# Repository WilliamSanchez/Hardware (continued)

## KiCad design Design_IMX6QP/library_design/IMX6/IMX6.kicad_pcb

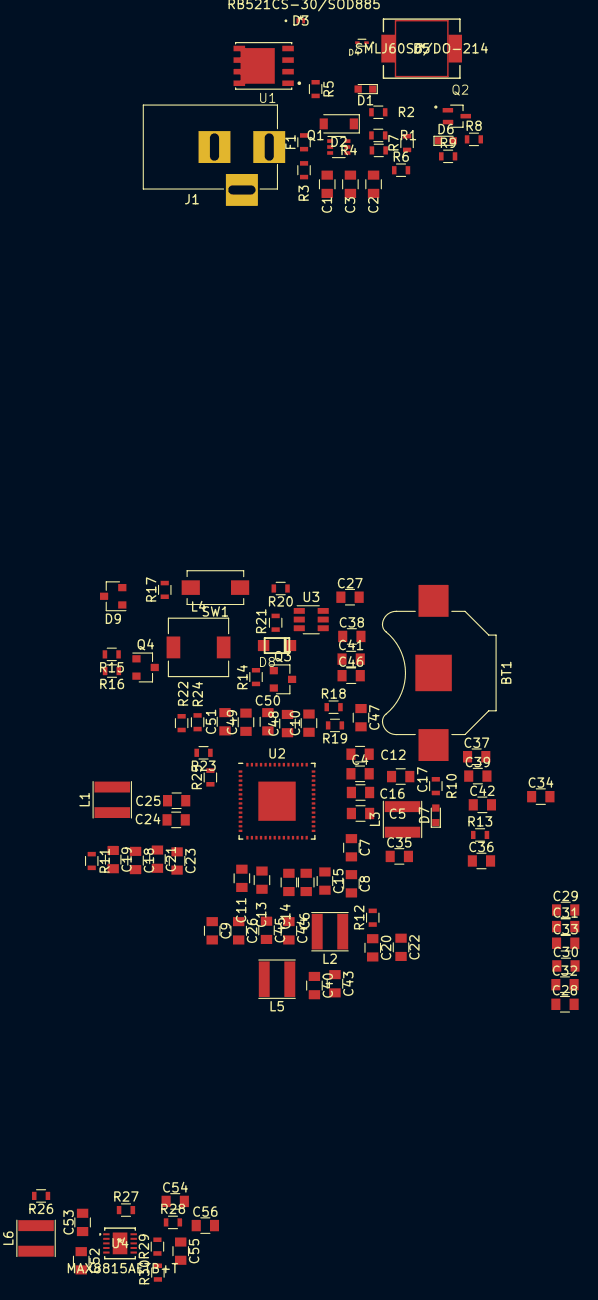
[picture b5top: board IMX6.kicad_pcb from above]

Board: 2 copper layers, 113 parts (0 on the bottom side), 71 nets, no tracks yet.

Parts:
BT1: Battery_Cell; Keystone_3000_1x12mm-CoinCell
C1: 100uF; C_0805
C2: 10uF; C_0805
C3: 1uF; C_0805
C4, C6, C9, C10: 0.47uF; C_0805
C5, C48, C50, C51: 1.0uF; C_0805
C7, C8, C12, C20, C22, C28, C29, C30, C31, C32, C33, C52, C53, C54, C56: 0.1uF; C_0805
C11, C13, C14, C15, C16, C17, C24, C25, C26, C27, C34, C35, C38, C40, C41, C43, C44, C45, C46: 4.7uF; C_0805
C18, C19, C21, C23, C36, C37, C39, C42, C55: 22uF; C_0805
C47: 10.0uF; C_0805
C49: 0.22uF; C_0805
D1, D6, D7: GREEN; LED_0603
D2: MMSZ5231BT1G; D_SOD-123
D3: RB521CS-30/SOD885; RB521CS30L_315
D4: ESD9L5/SOD-923; SODFL1006X40N
D5: SMLJ60S6/DO-214; SMLJ60S1-TP
D8: MBR140SFT; SOD-123FL
D9: BAT54C; SOT-23
F1: F500; R_0603
J1: 5V; BARREL_JACK
L1, L2, L3, L5: 1uH; L_Taiyo-Yuden_NR-40xx
L4: 2.2uH; L_6.3x6.3_H3
L6: 1.2uH; L_Taiyo-Yuden_NR-40xx
Q1: MBT3906DW1; SOT-363_SC-70-6
Q2: NTS4001NT1G; SOT65P220X100-3N
Q3: IRLML6402; SOT-23
Q4: 2N7002; SOT-23
R1, R6: 2.7K; R_0603
R2, R4: 100K; R_0603
R3, R7, R18, R19, R20, R21, R22, R24: 10K; R_0603
R5: 1.8K; R_0603
R8: 470K; R_0603
R9: 820; R_0603
R10, R14, R26, R27: 270; R_0603
R11, R12, R13: 0.02; R_0603
R15, R16: 10.0K; R_0603
R17, R29, R30: 0; R_0603
R23, R25: 68K; R_0603
R28: 100; R_0603
SW1: POWER; SW_SPST_EVQPE1
U1: FDMS6681Z; TRANS_FDMS0300S
U2: MMPF0100; QFN-56_EP_8x8_Pitch0.5mm
U3: FDC6321C_NL; TSOT-23-6
U4: MAX8815AETB+T; MAX8815AETB&plus_T

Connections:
GND: BT1.2, C1.2, C2.2, C3.2, C4.2, C5.2, C6.2, C8.2, C9.2, C10.2, C11.2, C12.2, C13.2, C14.2, C15.2, C16.2, C17.2, C18.2, C19.2, C20.2, C21.2, C22.2, C23.2, C24.2, C25.2, C26.2, C27.2, C28.2, C29.2, C30.2, C31.2, C32.2, C33.2, C34.2, C35.2, C36.2, C37.2, C38.2, C39.2, C40.2, C41.2, C42.2, C43.2, C44.2, C45.2, C46.2, C47.2, C48.2, C49.2, C50.2, C51.2, C52.2, C53.2, C54.2, C55.2, C56.2, D2.2, D4.2, D6.1, D7.1, J1.2, J1.3, Q2.2, R4.2, R8.2, R19.1, R20.2, R26.1, R27.1, R30.1, SW1.1, U2.5, U2.7, U2.14, U2.24, U2.25, U2.32, U2.48, U3.5, U4.5, U4.11
unnamed: BT1.1, C12.1, U2.42
unnamed: C1.1, C2.1, C3.1, D5.1, R9.1
unnamed: C4.1, U2.40
unnamed: C5.1, U2.31
unnamed: C6.1, U2.27
unnamed: C7.1, U2.30
unnamed: C7.2, C8.1, U2.29
unnamed: C9.1, U2.17
unnamed: C10.1, U2.43
unnamed: C11.1, U2.16
unnamed: C13.1, U2.18
unnamed: C14.1, U2.26
unnamed: C15.1, U2.28
unnamed: C16.1, U2.39
unnamed: C17.1, R10.2, U2.41
unnamed: C18.1, C19.1, C21.1, C23.1, L1.1, R11.1
unnamed: C20.1, C22.1, L2.1, R12.1
unnamed: C24.1, U2.12
unnamed: C25.1, U2.10
unnamed: C26.1, U2.23
unnamed: C28.1, C29.1, C30.1, C31.1, C32.1, C33.1
unnamed: C34.1, U2.37
unnamed: C35.1, U2.34
unnamed: C36.1, C37.1, C39.1, C42.1, L3.1, R13.1
unnamed: C38.1, C41.1, L4.1, Q3.3, U2.45
unnamed: C40.1, C43.1, L5.1
unnamed: C44.1, C45.1, U2.20
unnamed: C46.1, D8.1
unnamed: C47.1, R18.2
unnamed: C48.1, U2.49
unnamed: C49.1, U2.52
unnamed: C50.1, U2.51
unnamed: C51.1, U2.50
unnamed: C52.1, C53.1, L6.1, U4.3
unnamed: C54.1, R28.1, U4.7
unnamed: C55.1, C56.1, R28.2, R29.2, U4.9, U4.10
unnamed: D1.1, Q2.3
unnamed: D1.2, R5.2
unnamed: D2.1, R1.2, R3.1
unnamed: D3.1, Q1.4, R8.1, U1.4
unnamed: D3.2, Q1.1
unnamed: D4.1, D5.2, U1.5
unnamed: D6.2, R9.2
unnamed: D7.2, R10.1
unnamed: D8.2, L4.2
unnamed: D9.1, R21.2, U3.3, U3.6
unnamed: D9.3, R17.2, SW1.2
unnamed: F1.1, J1.1
unnamed: F1.2, Q1.3, Q1.6, R1.1, R6.1, U1.1, U1.2, U1.3
unnamed: L1.2, U2.8, U2.9, U2.11
unnamed: L2.2, U2.22
unnamed: L3.2, U2.35, U2.36
unnamed: L5.2, U2.21
unnamed: L6.2, U4.1, U4.2
unnamed: Q1.2, R3.2
unnamed: Q1.5, R7.2
unnamed: Q2.1, R2.2, R4.1
unnamed: Q3.1, Q4.3, R14.1
unnamed: Q3.2, R14.2
unnamed: Q4.1, R15.1, R16.1
unnamed: R6.2, R7.1
unnamed: R18.1, R19.2, U2.47
unnamed: R20.1, U3.1
unnamed: R21.1, U3.2
unnamed: R22.1, R24.2, U2.56
unnamed: R23.1, U2.1
unnamed: R25.1, U2.4
unnamed: R26.2, U4.4
unnamed: R27.2, U4.8
unnamed: R29.1, R30.2, U4.6

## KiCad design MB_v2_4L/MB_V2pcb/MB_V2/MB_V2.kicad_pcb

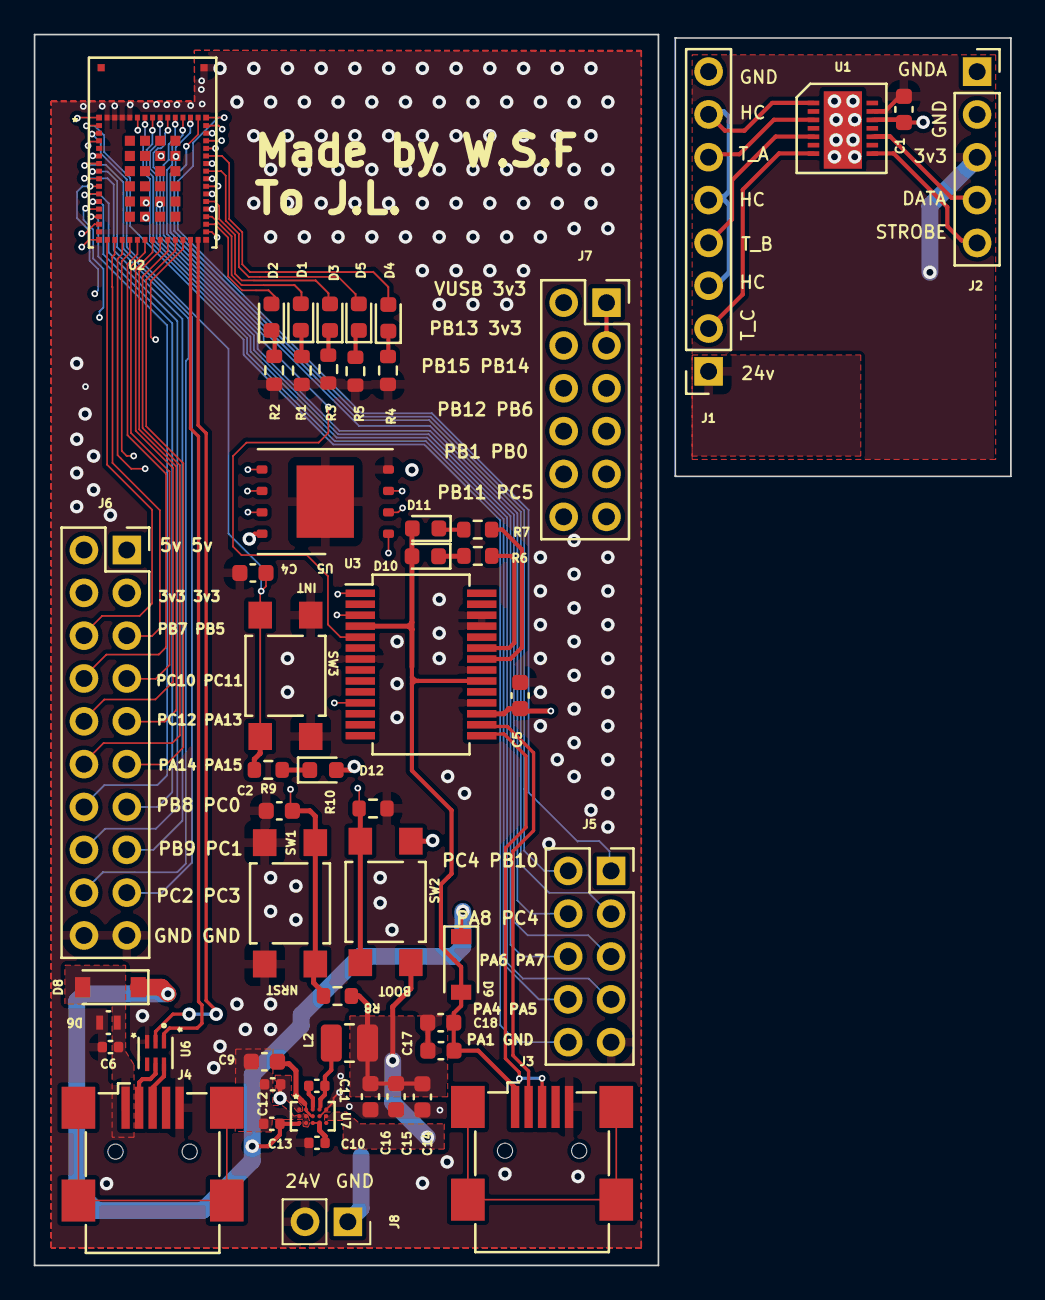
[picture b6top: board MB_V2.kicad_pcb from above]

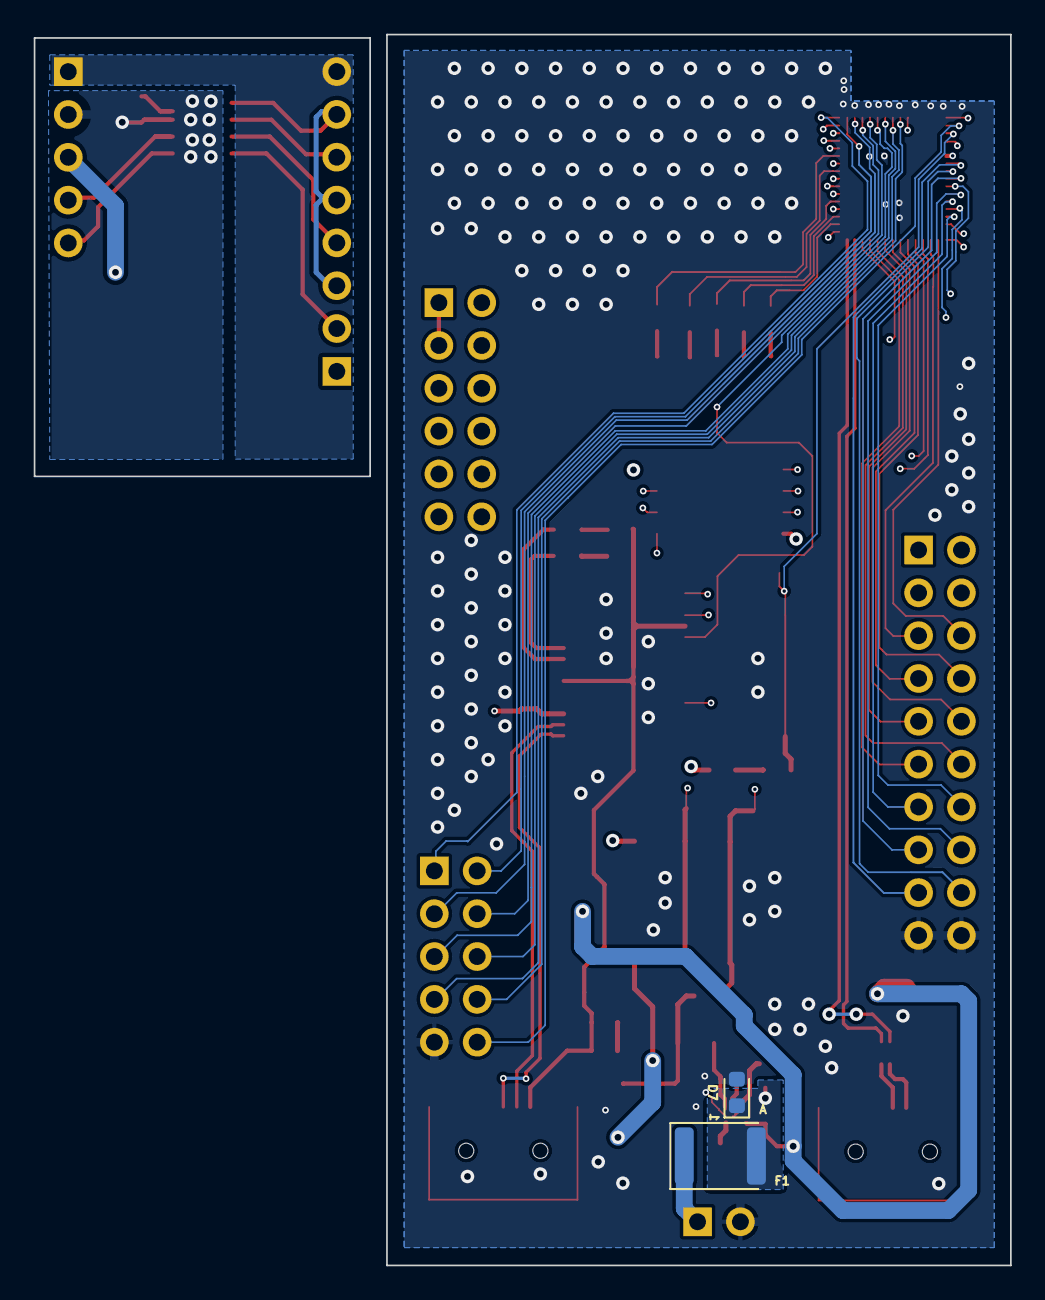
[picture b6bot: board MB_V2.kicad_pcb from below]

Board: 4 copper layers, 57.9 x 73.0 mm, 56 parts (2 on the bottom side), 85 nets.

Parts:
C1, C2, C4, C5, C18: 100nF; C_0603_1608Metric
C6: 100pF; C_0402_1005Metric
C9: 1uF (25v); C_0603_1608Metric
C10: 1uF (6v); C_0402_1005Metric
C11: 0.1uF (10V); C_0402_1005Metric
C12, C13: 2.2uF (25v); C_0402_1005Metric
C14, C15, C16: 22uF (10v); C_0603_1608Metric
C17: 1uF; C_0603_1608Metric
D1, D3: Red; LED_0603_1608Metric
D2: Green; LED_0603_1608Metric
D4: Yellow; LED_0603_1608Metric
D5: White; LED_0603_1608Metric
D6: ESD5Zxx; ESDA7P60-1U1M
D7: CPDU24V; D_0603_1608Metric
D8, D9: D_User; D_SOD-123
D10: Tx; LED_0603_1608Metric
D11: Rx; LED_0603_1608Metric
D12: Blue; LED_0603_1608Metric
F1: FS; D_1812_4532Metric
J1: Head_Magnetic_Card; PinSocket_1x08_P2.54mm_Vertical
J2: Host; PinSocket_1x05_P2.54mm_Vertical
J3, J4: USB_B_Micro; USB_Mini-B_Wuerth_65100516121_Horizontal
J5: PA; PinSocket_2x05_P2.54mm_Vertical
J6: PB; PinSocket_2x10_P2.54mm_Vertical
J7: PC; PinSocket_2x06_P2.54mm_Vertical
J8: source; PinSocket_1x02_P2.54mm_Vertical
L2: 10uH; L_1008_2520Metric
R1, R2, R3, R4, R5, R6, R7, R9: 300; R_0603_1608Metric
R8: 100k; R_0603_1608Metric
R10: 10k; R_0603_1608Metric
SW1: NRST; SW_SPST_TL3305A
SW2: BOOT; SW_SPST_TL3305A
SW3: INT; SW_SPST_TL3305A
U1: Magtek; MagTrack
U2: STM32WB5MMGH6TR
U3: FT232RL; SSOP-28_5.3x10.2mm_P0.65mm
U5: W25Q01JVZEIQ; WSON-8-1EP_8x6mm_P1.27mm_EP3.4x4.3mm
U6: ECMF02-2AMX6
U7: MAX77756CEWL+T; MAX77756CEWL&plus_T

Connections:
5V_Prog: C13.1, D8.1 (K), D9.1 (K), J6.1, J6.2, U7.C1 (IN2)
+3V3: C1.1, C5.2, C14.1, C15.1, C16.1, D12.2 (A), J2.3, J6.3, J6.4, J7.1, J7.3, L2.2, R8.1, SW2.1, U1.13 (VDD), U2.4 (VREF+), U2.6 (VDDA), U2.15 (VBAT), U2.17 (VDDA), U3.17 (3V3OUT), U5.8 (VCC), U7.B5 (OUT/FB)
+24V: C12.1, D7.1 (K), F1.2, J1.1, U7.A1 (IN1)
/STM32BLE/BOOT0: R10.1, SW2.2, U2.13 (PH3-BOOT0)
/STM32BLE/INT: C4.2, R9.2, SW3.1, U2.3 (PA0)
/STM32BLE/Modulo_conn/5v_USB_User: C6.2, D6.1 (K), D8.2 (A), J4.1 (VBUS)
/STM32BLE/Modulo_conn/Prog_+: J3.3 (D+), U3.15 (USBD+)
/STM32BLE/Modulo_conn/Prog_-: J3.2 (D-), U3.16 (USBD-)
/STM32BLE/NRST: C2.2, R8.2, SW1.1, U2.10 (NRST)
/Track_Mag/DATA: J2.4, U1.10 (DATA)
/Track_Mag/HC: J1.3, J1.5, J1.7, U1.1 (HEAD_COMMOMN)
/Track_Mag/STROBE: J2.5, U1.8 (STROBE)
/Track_Mag/Track_A: J1.6, U1.3 (HEAD_A)
/Track_Mag/Track_B: J1.4, U1.5 (HEAD_B)
/Track_Mag/Track_C: J1.2, U1.7 (HEAD_C)
GND: C1.2, C2.1, C4.1, C5.1, C6.1, C9.2, C10.2, C12.2, C13.2, C14.2, C15.2, C16.2, C17.1, C18.1, D6.2 (A), D7.2 (A), J2.2, J3.5 (GND), J4.5 (GND), J5.9, J6.19, J6.20, J8.2, R1.2, R2.2, R3.2, R4.2, R5.2, R10.2, SW1.2, SW3.2, U1.12 (VSS), U1.15 (GND), U2.5 (VSS), U2.16 (VSS), U2.31 (VSS), U2.57 (VSS), U2.58 (ANT_IN), U2.59 (RF_OUT), U2.60 (VSS), U2.84 (VSS), U2.86 (VSS), U3.7 (GND), U3.18 (GND), U3.21 (GND), U3.25 (AGND), U3.26 (TEST), U5.4 (GND), U5.9 (EP), U6.3 (GND), U7.A5 (PGND), U7.B1 (VIO), U7.B2 (SDA), U7.B4 (AGND), U7.C2 (SCL)
GNDA: J1.8, J2.1
LD-WT: D5.2 (A), U2.40 (PC13)
LD_BL: D1.2 (A), U2.34 (PD1)
LD_GR: D2.2 (A), U2.33 (PD0)
LD_RD: D3.2 (A), U2.36 (PC6)
LD_YW: D4.2 (A), U2.42 (PE4)
MEM_CS: U2.1 (PA2), U5.1 (~CS)
MEM_IO0/DI: U2.73 (PD4), U5.5 (DI(IO0))
MEM_IO1/DO: U2.80 (PD5), U5.2 (DO(IO1))
MEM_IO2/WP: U2.81 (PD6), U5.3 (IO2)
MEM_IO3/HOLD: U2.67 (PD7), U5.7 (IO3)
MEM_SCK: U2.56 (PA3), U5.6 (CLK)
unnamed: C9.1, U7.A2 (SUP), U7.B3 (EN)
unnamed: C10.1, U7.C3 (BIAS), U7.C4 (ILIM)
unnamed: C11.1, U7.A3 (BST)
unnamed: C11.2, L2.1, U7.A4 (LX)
unnamed: C17.2, C18.2, D9.2 (A), D10.2 (A), D11.2 (A), J3.1 (VBUS), U3.4 (VCCIO), U3.20 (VCC)
unnamed: D1.1 (K), R1.1
unnamed: D2.1 (K), R2.1
unnamed: D3.1 (K), R3.1
unnamed: D4.1 (K), R4.1
unnamed: D5.1 (K), R5.1
unnamed: D10.1 (K), R6.1
unnamed: D11.1 (K), R7.1
unnamed: D12.1 (K), R9.1
unnamed: F1.1, J8.1
unnamed: J4.2 (D-), U6.5 (D-)
unnamed: J4.3 (D+), U6.6 (D+)
unnamed: R6.2, U3.23 (CBUS0)
unnamed: R7.2, U3.22 (CBUS1)
PA1: J5.10, U2.2 (PA1)
PA4: J5.8, U2.55 (PA4)
PA5: J5.7, U2.54 (PA5)
PA6: J5.6, U2.53 (PA6)
PA7: J5.5, U2.52 (PA7)
PA8: J5.4, U2.50 (PA8)
PA13: J6.9, U2.25 (PA13)
PA14: J6.12, U2.26 (PA14)
PA15: J6.11, U2.27 (PA15)
PB0: J7.9, U2.43 (PB0)
PB1: J7.10, U2.44 (PB1)
PB2: J5.2, U2.48 (PB2)
PB5: J6.5, U2.19 (PB5)
PB6: J7.7, U2.39 (PB6)
PB7: J6.6, U2.18 (PB7)
PB8: J6.14, U2.14 (PB8)
PB9: J6.16, U2.11 (PB9)
PB10: J5.1, U2.47 (PB10)
PB11: J7.12, U2.46 (PB11)
PB12: J7.8, U2.41 (PB12)
PB13: J7.4, U2.35 (PB13)
PB14: J7.5, U2.37 (PB14)
PB15: J7.6, U2.38 (PB15)
PC0: J6.13, U2.12 (PC0)
PC1: J6.15, U2.9 (PC1)
PC2: J6.18, U2.8 (PC2)
PC3: J6.17, U2.7 (PC3)
PC4: J5.3, U2.49 (PC4)
PC5: J7.11, U2.45 (PC5)
PC10: J6.8, U2.22 (PC10)
PC11: J6.7, U2.23 (PC11)
PC12: J6.10, U2.24 (PC12)
USART_CTS: U2.20 (PB4), U3.3 (RTS)
USART_RTS_DE: U2.21 (PB3), U3.11 (CTS)
USART_RX: U2.28 (PA10), U3.1 (TXD)
USART_TX: U2.51 (PA9), U3.5 (RXD)
USB_N: U2.30 (PA11), U6.2 (D-)
USB_P: U2.29 (PA12), U6.1 (D+)
VDDUSB: J7.2, U2.32 (VDDUSB)

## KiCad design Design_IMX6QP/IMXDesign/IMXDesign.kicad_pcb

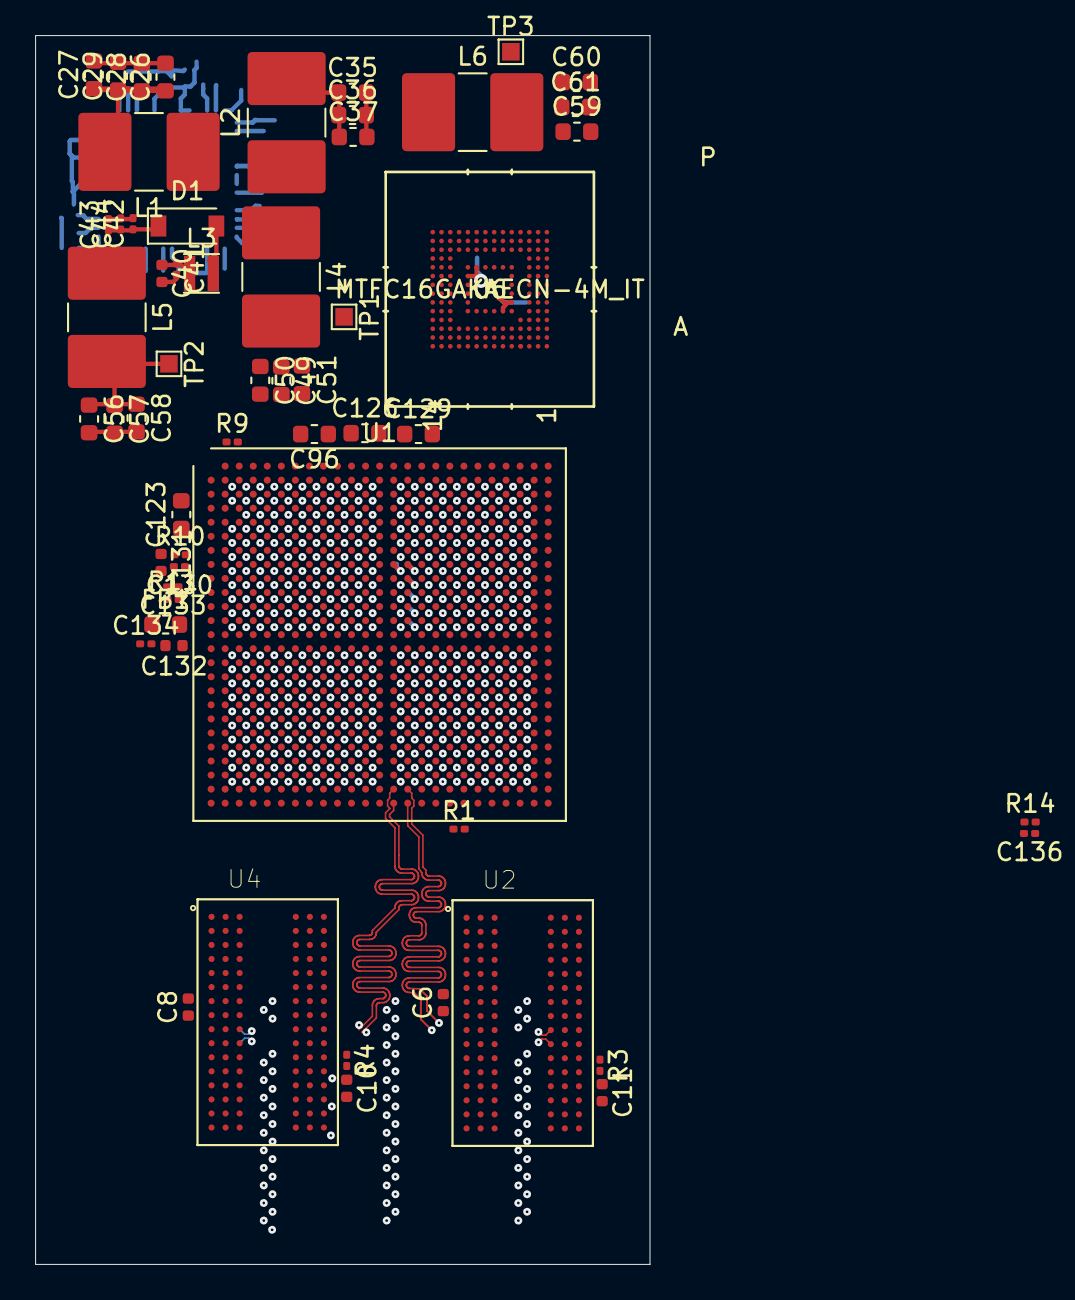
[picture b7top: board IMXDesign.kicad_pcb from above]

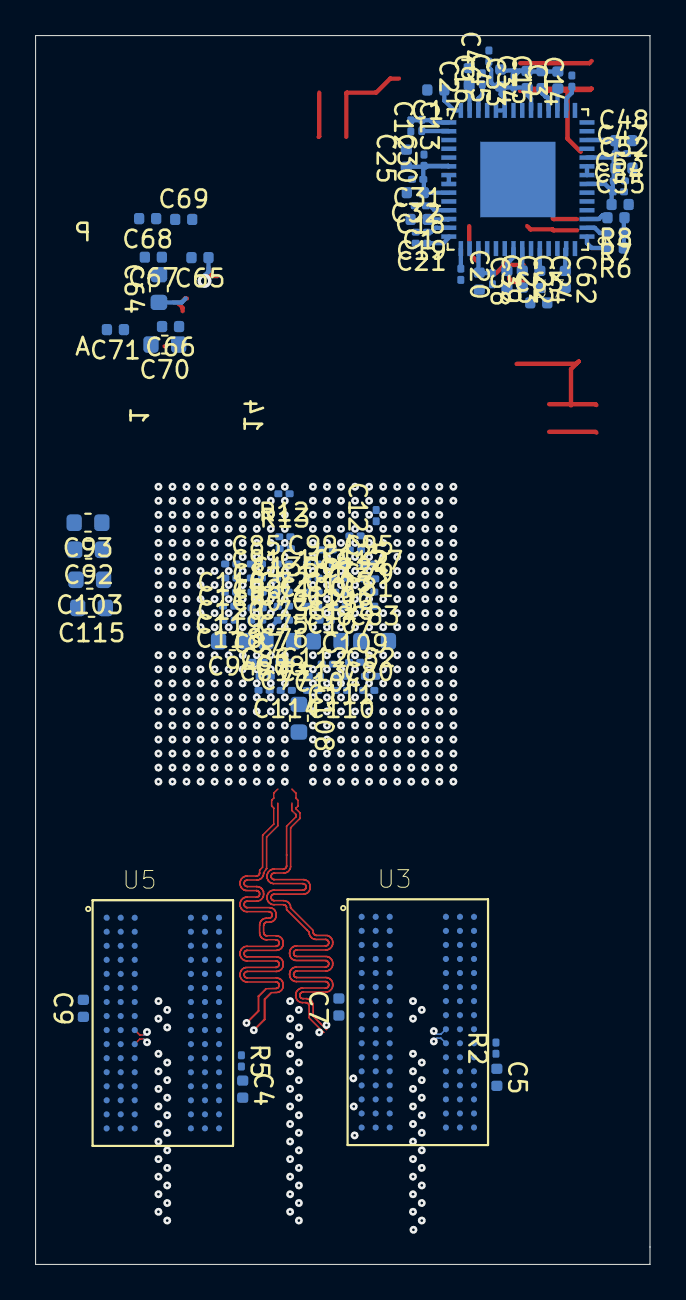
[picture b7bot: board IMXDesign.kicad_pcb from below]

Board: 8 copper layers, 35.0 x 70.0 mm, 168 parts (111 on the bottom side), 109 nets.

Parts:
C1, C2, C3: 1uf; C_0402_1005Metric
C4, C5, C6, C7, C8, C9, C10, C11: 220nF; C_0402_1005Metric
C12, C13, C21, C30, C31, C33, C39, C41, C46, C47, C53, C54: 100nF; C_0201_0603Metric
C14, C16, C18, C19: 2.2uF; C_0201_0603Metric
C15, C17, C25, C32, C34, C40, C45, C48, C52, C55, C131, C132: 4.7uF; C_0402_1005Metric
C20: 0.47uF; C_0201_0603Metric
C22, C23, C24, C62, C63: 1uF; C_0402_1005Metric
C26, C27, C28, C29, C35, C36, C37, C49, C50, C51, C56, C57, C58, C59, C60, C61, C78, C83, C92, C93, C94, C96, C98, C103, C108, C115, C123, C126, C129: 22uF; C_0603_1608Metric
C38: 2.2uF; C_0402_1005Metric
C42, C127: 10nF; C_0201_0603Metric
C43, C44: 22uF; C_0201_0603Metric
C64, C70: 4.7uF; C_0603_1608Metric
C65, C66, C67, C68, C69, C71: 100nF; C_0402_1005Metric
C72, C73, C74, C75, C76, C77, C79, C80, C81, C82, C84, C85, C86, C87, C88, C89, C90, C91, C95, C97, C99, C100, C101, C102, C104, C105, C106, C107, C109, C110, C111, C112, C113, C114, C116, C117, C118, C119, C120, C121, C122, C124, C128, C130, C133, C134, C135, C136: 220nF; C_0201_0603Metric
C125: 10uF; C_0201_0603Metric
D1: MBR140SFT1G; D_SOD-123
FB1: 220R, 2.5A; Fuse_0603_1608Metric
L1, L2, L4, L5, L6: 1uH; L_2816_7142Metric
L3: 2.2uH; L_Taiyo-Yuden_NR-20xx
R1, R2, R3, R4, R5: 240; R_0201_0603Metric
R6, R7, R8: 100k; R_0402_1005Metric
R9: 200; R_0201_0603Metric
R10, R11, R13, R14: 0; R_0201_0603Metric
R12: 191; R_0201_0603Metric
TP1, TP3: 3v3; TestPoint_Pad_1.0x1.0mm
TP2: 1v375; TestPoint_Pad_1.0x1.0mm
U1: MCIMX6QP5EVT; BGA-624_21.0x21.0mm_Layout25x25_P0.8mm
U2, U3, U4, U5: MT41K128M16JT-107_K; BGA80P96C6X16_800X1400X110
U6: MTFC16GAKAECN-4M_IT; MTFC16GAKAECN-4M IT
U7: W_MMPF0100; QFN50P800X800X100-57N

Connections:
+0v75_DDR: C35.1, C36.1, C37.1, L2.2, U7.19
+1v5_DDR: C12.1, C26.1, C27.1, C28.1, C29.1, L1.2, U2.A1, U2.A8, U2.B2, U2.C1, U2.C9, U2.D2, U2.D9, U2.E9, U2.F1, U2.G7, U2.H2, U2.H9, U2.K2, U2.K8, U2.N1, U2.N9, U2.R1, U2.R9, U3.A1, U3.A8, U3.B2, U3.C1, U3.C9, U3.D2, U3.D9, U3.E9, U3.F1, U3.G7, U3.H2, U3.H9, U3.K2, U3.K8, U3.N1, U3.N9, U3.R1, U3.R9, U4.A1, U4.A8, U4.B2, U4.C1, U4.C9, U4.D2, U4.D9, U4.E9, U4.F1, U4.G7, U4.H2, U4.H9, U4.K2, U4.K8, U4.N1, U4.N9, U4.R1, U4.R9, U5.A1, U5.A8, U5.B2, U5.C1, U5.C9, U5.D2, U5.D9, U5.E9, U5.F1, U5.G7, U5.H2, U5.H9, U5.K2, U5.K8, U5.N1, U5.N9, U5.R1, U5.R9, U7.30, U7.38
+1v375_SOC: C56.1, C57.1, C58.1, C59.1, C60.1, C61.1, L5.2, L6.2, TP2.1, TP3.1, U7.6, U7.13
+3V3: C1.1, C2.1, C49.1, C50.1, C51.1, C62.1, L4.2, TP1.1, U7.25, U7.27, U7.40, U7.55
+5V: C42.1, C43.1, C44.1, D1.1, U7.44
/DDR3_Memory/CPU_DDR3/+DDR_VREF: U1.R18, U1.T18, U1.U18, U1.V9, U1.V10, U1.V11, U1.V12, U1.V13, U1.V14, U1.V15, U1.V16, U1.V17, U1.V18
/DDR3_Memory/CPU_DDR3/DRAM_A0: U1.AC14, U2.N3, U3.N3, U4.N3, U5.N3
/DDR3_Memory/CPU_DDR3/DRAM_A1: U1.AB14, U2.P7, U3.P7, U4.P7, U5.P7
/DDR3_Memory/CPU_DDR3/DRAM_A2: U1.AA14, U2.P3, U3.P3, U4.P3, U5.P3
/DDR3_Memory/CPU_DDR3/DRAM_A3: U1.Y14, U2.N2, U3.N2, U4.N2, U5.N2
/DDR3_Memory/CPU_DDR3/DRAM_A4: U1.W14, U2.P8, U3.P8, U4.P8, U5.P8
/DDR3_Memory/CPU_DDR3/DRAM_A5: U1.AE13, U2.P2, U3.P2, U4.P2, U5.P2
/DDR3_Memory/CPU_DDR3/DRAM_A6: U1.AC13, U2.R8, U3.R8, U4.R8, U5.R8
/DDR3_Memory/CPU_DDR3/DRAM_A7: U1.Y13, U2.R2, U3.R2, U4.R2, U5.R2
/DDR3_Memory/CPU_DDR3/DRAM_A8: U1.AB13, U2.T8, U3.T8, U4.T8, U5.T8
/DDR3_Memory/CPU_DDR3/DRAM_A9: U1.AE12, U2.R3, U3.R3, U4.R3, U5.R3
/DDR3_Memory/CPU_DDR3/DRAM_A10: U1.AA15, U2.L7, U3.L7, U4.L7, U5.L7
/DDR3_Memory/CPU_DDR3/DRAM_A11: U1.AC12, U2.R7, U3.R7, U4.R7, U5.R7
/DDR3_Memory/CPU_DDR3/DRAM_A12: U1.AD12, U2.N7, U3.N7, U4.N7, U5.N7
/DDR3_Memory/CPU_DDR3/DRAM_A13: U1.AC17, U2.T3, U3.T3, U4.T3, U5.T3
/DDR3_Memory/CPU_DDR3/DRAM_A14: U1.AA12, U3.M2
/DDR3_Memory/CPU_DDR3/DRAM_A15: U1.Y12, U3.N8
/DDR3_Memory/CPU_DDR3/DRAM_D0: U1.AD2, U3.E3
/DDR3_Memory/CPU_DDR3/DRAM_D1: U1.AE2, U3.F7
/DDR3_Memory/CPU_DDR3/DRAM_D2: U1.AC4, U3.F2
/DDR3_Memory/CPU_DDR3/DRAM_D3: U1.AA5, U3.F8
/DDR3_Memory/CPU_DDR3/DRAM_D4: U1.AC1, U3.H3
/DDR3_Memory/CPU_DDR3/DRAM_D5: U1.AD1, U3.H8
/DDR3_Memory/CPU_DDR3/DRAM_D6: U1.AB4, U3.G2
/DDR3_Memory/CPU_DDR3/DRAM_D7: U1.AE4, U3.H7
/DDR3_Memory/CPU_DDR3/DRAM_D8: U1.AD5, U3.D7
/DDR3_Memory/CPU_DDR3/DRAM_D9: U1.AE5, U3.C3
/DDR3_Memory/CPU_DDR3/DRAM_D10: U1.AA6, U3.C8
/DDR3_Memory/CPU_DDR3/DRAM_D11: U1.AE7, U3.C2
/DDR3_Memory/CPU_DDR3/DRAM_D12: U1.AB5, U3.A7
/DDR3_Memory/CPU_DDR3/DRAM_D13: U1.AC5, U3.A2
/DDR3_Memory/CPU_DDR3/DRAM_D14: U1.AB6, U3.B8
/DDR3_Memory/CPU_DDR3/DRAM_D15: U1.AC7, U3.A3
/DDR3_Memory/CPU_DDR3/DRAM_SDCLK_0+: U1.AD15, U2.J7, U5.J7
/DDR3_Memory/CPU_DDR3/DRAM_SDCLK_0-: U1.AE15, U2.K7, U5.K7
/DDR3_Memory/CPU_DDR3/DRAM_SDCLK_1+: U1.AD14, U3.J7, U4.J7
/DDR3_Memory/CPU_DDR3/DRAM_SDCLK_1-: U1.AE14, U3.K7, U4.K7
/SDx_INTERFACE/SD#/SD_CLK: U1.E16, U6.M6
/SDx_INTERFACE/SD#/SD_D0: U1.D18, U6.A3
/SDx_INTERFACE/SD#/SD_D1: U1.B19, U6.A4
/SDx_INTERFACE/SD#/SD_D2: U1.F17, U6.A5
/SDx_INTERFACE/SD#/SD_D3: U1.A20, U6.B2
/SDx_INTERFACE/SD#/SD_D4: U1.E18, U6.B3
/SDx_INTERFACE/SD#/SD_D5: U1.C19, U6.B4
/SDx_INTERFACE/SD#/SD_D6: U1.B20, U6.B5
/SDx_INTERFACE/SD#/SD_D7: U1.D19, U6.B6
/SourcePower/3v3_LICELL: C21.1, U7.42
/SourcePower/+3v0_VSNS: C20.1, R6.1, R7.1, R8.1, U7.43
/SourcePower/SWBSTLX: D1.2, L3.2, U7.46
DDR_VREF: C4.1, C5.1, C6.1, C7.1, C8.1, C9.1, C10.1, C11.1, U2.H1, U2.M8, U3.H1, U3.M8, U4.H1, U4.M8, U5.H1, U5.M8, U7.31
GND: C1.2, C2.2, C3.2, C4.2, C5.2, C6.2, C7.2, C8.2, C9.2, C10.2, C11.2, C13.2, C14.2, C15.2, C16.2, C17.2, C18.2, C19.2, C20.2, C21.2, C22.2, C23.2, C24.2, C25.2, C26.2, C27.2, C28.2, C29.2, C30.2, C31.2, C32.2, C33.2, C34.2, C35.2, C36.2, C37.2, C38.2, C39.2, C40.2, C41.2, C42.2, C43.2, C44.2, C45.2, C46.2, C47.2, C48.2, C49.2, C50.2, C51.2, C52.2, C53.2, C54.2, C55.2, C56.2, C57.2, C58.2, C59.2, C60.2, C61.2, C62.2, C63.2, C64.2, C65.2, C66.2, C67.2, C68.2, C69.2, C70.2, C71.2, C72.2, C73.2, C74.2, C75.2, C76.2, C77.2, C78.2, C79.2, C80.2, C81.2, C82.2, C83.2, C84.2, C85.2, C86.2, C87.2, C88.2, C89.2, C90.2, C91.2, C92.2, C93.2, C94.2, C95.2, C96.2, C97.2, C98.2, C99.2, C100.2, C101.2, C102.2, C103.2, C104.2, C105.2, C106.2, C107.2, C108.2, C109.2, C110.2, C111.2, C112.2, C113.2, C114.2, C115.2, C116.2, C117.2, C118.2, C119.2, C120.2, C121.2, C122.2, C123.2, C124.2, C125.2, C126.2, C127.2, C128.2, C129.2, C130.2, C131.2, C132.2, C133.2, C134.2, C135.2, C136.2, R1.2, R2.2, R3.2, R4.2, R5.2, R9.2, R12.2, U1.A4, U1.A8, U1.A13, U1.A25, U1.AA7, U1.AA10, U1.AA13, U1.AA16, U1.AA19, U1.AA22, U1.AB3, U1.AB24, U1.AD4, U1.AD7, U1.AD10, U1.AD13, U1.AD16, U1.AD19, U1.AD22, U1.AE1, U1.AE25, U1.B4, U1.C1, U1.C4, U1.C6, U1.C10, U1.D3, U1.D6, U1.D8, U1.E5, U1.E6, U1.E7, U1.F5, U1.F6, U1.F7, U1.F8, U1.G3, U1.G10, U1.G19, U1.H8, U1.H12, U1.H15, U1.H18, U1.J2, U1.J8, U1.J12, U1.J15, U1.J18, U1.K8, U1.K10, U1.K12, U1.K15, U1.K18, U1.L2, U1.L5, U1.L8, U1.L10, U1.L12, U1.L15, U1.L18, U1.M8, U1.M10, U1.M12, U1.M15, U1.M18, U1.N8, U1.N10, U1.N15, U1.N18, U1.P8, U1.P10, U1.P12, U1.P15, U1.P18, U1.R8, U1.R12, U1.R15, U1.R17, U1.T8, U1.T11, U1.T12, U1.T15, U1.T17, U1.T19, U1.U8, U1.U11, U1.U12, U1.U15, U1.U17, U1.U19, U1.V8, U1.V19, U1.W3, U1.W7, U1.W8, U1.W9, U1.W10, U1.W11, U1.W12, U1.W13, U1.W15, U1.W16, U1.W17, U1.W18, U1.W19, U1.Y5, U1.Y24, U2.A9, U2.B1, U2.B3, U2.B9, U2.D1, U2.D8, U2.E1, U2.E2, U2.E8, U2.F9, U2.G1, U2.G8, U2.G9, U2.J2, U2.J8, U2.M1, U2.M9, U2.P1, U2.P9, U2.T1, U2.T9, U3.A9, U3.B1, U3.B3, U3.B9, U3.D1, U3.D8, U3.E1, U3.E2, U3.E8, U3.F9, U3.G1, U3.G8, U3.G9, U3.J2, U3.J8, U3.M1, U3.M9, U3.P1, U3.P9, U3.T1, U3.T9, U4.A9, U4.B1, U4.B3, U4.B9, U4.D1, U4.D8, U4.E1, U4.E2, U4.E8, U4.F9, U4.G1, U4.G8, U4.G9, U4.J2, U4.J8, U4.M1, U4.M9, U4.P1, U4.P9, U4.T1, U4.T9, U5.A9, U5.B1, U5.B3, U5.B9, U5.D1, U5.D8, U5.E1, U5.E2, U5.E8, U5.F9, U5.G1, U5.G8, U5.G9, U5.J2, U5.J8, U5.M1, U5.M9, U5.P1, U5.P9, U5.T1, U5.T9, U6.A6, U6.C4, U6.E7, U6.G5, U6.H10, U6.J5, U6.K8, U6.N2, U6.N5, U6.P4, U6.P6, U7.5, U7.14, U7.15, U7.32, U7.48, U7.57
unnamed: C3.1, U7.17
unnamed: C22.1, U7.50
unnamed: C23.1, U7.49
unnamed: C24.1, U7.52
unnamed: C40.1, C41.1, L3.1
unnamed: C63.1, U7.51
unnamed: C64.1, C65.1, C66.1, U6.E6, U6.F5, U6.J10, U6.K9
unnamed: C67.1, C68.1, C69.1, C70.1, U6.C6, U6.M4, U6.N4, U6.P3, U6.P5
unnamed: C71.1, U6.C2
unnamed: C72.1, C73.1, C74.1, C75.1, C76.1, C77.1, C78.1, U1.H14, U1.J14, U1.K14, U1.L14, U1.M14, U1.N14, U1.P14, U1.R14
unnamed: C79.1, C80.1, C81.1, C82.1, C83.1, U1.K9, U1.L9, U1.M9, U1.N9, U1.P9, U1.R9, U1.T9, U1.U9
unnamed: C84.1, C85.1, C86.1, C87.1, C88.1, C89.1, C90.1, C91.1, C92.1, C93.1, C94.1, U1.H16, U1.J16, U1.K16, U1.L16, U1.M16, U1.N16, U1.P16, U1.R16, U1.T16, U1.U16
unnamed: C95.1, C96.1, U1.H9, U1.J9
unnamed: C97.1, U1.G11
unnamed: C98.1, C99.1, C100.1, C101.1, C102.1, U1.H13, U1.J13, U1.K13, U1.L13, U1.M13, U1.N13, U1.P13, U1.R13
unnamed: C103.1, C104.1, C105.1, C106.1, C107.1, U1.H11, U1.J11, U1.K11, U1.L11, U1.M11, U1.N11, U1.P11, U1.R11
unnamed: C108.1, C109.1, C110.1, C111.1, C112.1, C113.1, C114.1, U1.R10, U1.T10, U1.T13, U1.T14, U1.U10, U1.U13, U1.U14
unnamed: C115.1, C116.1, C117.1, C118.1, C119.1, C120.1, U1.H17, U1.J17, U1.K17, U1.L17, U1.M17, U1.N17, U1.P17
unnamed: C121.1, U1.N12
unnamed: C122.1, C123.1, U1.E8
unnamed: C124.1, U1.G9
unnamed: C125.1, C126.1, U1.F9
unnamed: C127.1, C128.1, C129.1, U1.H10, U1.J10
unnamed: C130.1, R10.2, U1.G7
unnamed: C131.1, R10.1
unnamed: C132.1, FB1.2, R11.1
unnamed: C133.1, R11.2, U1.H7
unnamed: C134.1, FB1.1, U1.G8
unnamed: C135.1, R13.2, U1.G13
unnamed: C136.1, R14.2, U1.G12
unnamed: L1.1, U7.35, U7.36
unnamed: L2.1, U7.21
unnamed: L4.1, U7.22
unnamed: L5.1, U7.11
unnamed: L6.1, U7.8, U7.9
unnamed: R1.1, U1.AE17
unnamed: R2.1, U3.L8
unnamed: R3.1, U2.L8
unnamed: R4.1, U4.L8
unnamed: R5.1, U5.L8
unnamed: R7.2, U7.2
unnamed: R9.1, U1.A2
unnamed: R12.1, U1.C14
PMIC_INT_B: R6.2, U7.1
PMIC_VHALF: C12.2, C13.1, U7.29
POR_B: R8.2, U7.3
SYS_4V2: C25.1, C30.1, C31.1, C32.1, C33.1, C34.1, C38.1, C39.1, C45.1, C46.1, C47.1, C48.1, C52.1, C53.1, C54.1, C55.1, U7.7, U7.10, U7.12, U7.20, U7.23, U7.24, U7.34, U7.37, U7.45
VGEN1_1v35: C14.1, U7.16
VGEN2_1v35: C15.1, U7.18
VGEN3_1v35: C16.1, U7.26
VGEN4_1v35: C17.1, U7.28
VGEN5_1v35: C18.1, U7.39
VGEN6_1v35: C19.1, U7.41

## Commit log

2023-09-26 Add design IMX8 PCB
2023-10-08 Adding color on LPDDR4 memory net
2023-10-12 Add library to WIFI/BLE
2023-10-14 changes vias pad size
2023-10-15 Update IMX6QP and IMX8MQ
2023-10-22 Add QSPI and more color
2023-11-02 it was inserted power control system
2024-09-20 Add new progject based on chip MIMX8ML plus with 4 cores, idealy for IoT with eight layers as recommended
2024-10-06 Add power system tracing and nets
2024-10-06 Add storage unit
2024-10-17 Add resistors to PMIC
2024-10-19 Add interface io pins
2024-10-26 processor capacitors location
2024-11-02 assign net classdevice
2024-11-03 changes memory foot print
2024-11-14 Changes the contector for DF40C-100Dx
2024-11-17 Update schematic and add ethernet interface ksz9131rn
2024-11-17 Add power layer
2024-11-23 Improve and fix connections in LPPDR4 memory
2025-01-11 Add Base board IMxM8ML project
2025-01-11 Add gitignore
2025-01-11 Refresh gitignore
2025-01-25 Add SPB228 WIFI/BLE module
2025-02-16 Improve power source module in the base board
2025-02-23 improving the usb conector
2025-03-02 improving Ethernet, USB and Camera inteface
2025-03-18 Add LVDs and CSI Interface
2025-03-23 Adds audio interface
2025-05-02 Review
2025-06-19 reorganization of the componentes
2025-06-20 Board base resize
2025-06-23 pcb reorganization
2025-06-29 CPU Board actualizate
2025-07-05 [IMX8ML-Processor] Reorganization of the pinout conector since processor to conectors
2025-07-13 [PROCESSOR] Create zones It added power zones in the four layer
2025-07-21 [IMX8ML-CPU] LPDDR4 memories reorganization of track between processor and memories.
2025-07-27 [CPU/BB] Improving the conection between the cpu and BB
    * Reorganization of the components in the Base board.
2025-08-24 [BB_IMX8MLP IMX8MLP] Actuallizated to 9.0 kicad version
2025-08-31 [LoRa] Starting a new project
    Starting a new project base on LoRa LR1121, this project use
    the module LBAA0XV2GT-001 that had sub-GHz and 2.4GHz frequencies.
2025-09-14 [LR1121] Add GPS in the project
    GPS and power module was add in the project
2025-09-20 [PCB] Inster power module in the PCB
    It was improve the power module
    .
2025-09-28 [PMIC] Changes PMIC chip to LTC4146 for BQ25619
    The BQ25619 is now the PMIC because it had 3.5v-4.5v
2025-10-17 [BB_IMX8ML] Change MCU F280015x
    Change MCU STM32H5 for F2800157 dual core real-time
2026-02-17 [BB_IMX8ML] It was reoganizated the device position
    It was reorganized the devices to improve the routing.
2026-04-24 [IMX8ML] Add new layer
    A new layers was add in the cpu schematic, now it had 8 layer.
